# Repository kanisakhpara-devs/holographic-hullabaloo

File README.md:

# Holographic Hullabaloo
A spinning LED (Persistence of Vision) desk assistant which creates a "holographic" sarcastic 3D desk buddy.

### what is he talking about?

I understand your possibly dire confusion, so I'll try my best to explain it in the simplest way possible. Have you ever seen those LED fans which are all over Insta? They spin, to create an image.

The problem, however with those, is that they can only be viewed from one side, and properly from only one angle. Instead of engineering the solution, they are simply stuck on your wall, so it is only possible to view it from that exact point. Sometimes the best solutions are the most simple ones. Not in this case.

From this failure of a potential innovation sprouted a not very original, but a not-widely-done idea of an LED fan, but 3D, with AI integration, and sarcasm.

One may ask, why on earth would he do such a thing which would force him to spend hours upon hours coding and tuning the expression sequence loop? The short answer is, I'm speedrunning carpal tunnel. The long answer is that it would usually annoy me when those viral fans would call themselves high-tech, and 3d image viewer, and stuff like that, and nearly everyone who would buy them would end up disappointed. Or with their hand chopped off. But I built this mostly because it would look cool on my desk. (i hope u know im kidding)

$\color{orange}{\textsf{3D image + offline AI + Sass = Holographic Hullabaloo}}$
### how does it work?
2 blades with each a singular column of 72 LEDs, directly opposite each other, spin around a pivot at 1500 RPM, driven by a 775 motor, and rapidly flash in a coded sequence to create an image of a floating 3D face, which expresses and talks to you by recording your voice through the mic in the base, sending the audio through a USB cable to the laptop, where it gets transcribed and answered by a local Ollama-routed Gemma 3:4b, and then sending the answer back so the device speaks to you. Each response comes with an emotion tag, which tells the onboard ESP which expression to change to.

### how do I use it?
1. Plug in the 12V adapter to a wallsocket.
2. Connect the USB-C to the laptop. It should be recognized as a sound card.
3. Start the desktop app (Windows only, yet to be built)
4. Walk up to it and use the push-to-talk button (Wakeword will be toggleable)
5. When it senses that no one is around, it will stop spinning on its own in 10 minutes.

<details>
<summary>specs table</summary>

| Spec | Value |
| --- | --- |
| Display | Cylindrical POV, 100 mm across, 180 mm tall |
| Blades | 2, opposite each other at 50 mm radius |
| LEDs | 72 x APA102-2020 per blade (144 total), 2.5 mm pitch |
| Resolution | 72 rows x 200 columns per spin |
| Pixel size | 2.5 mm tall x 1.57 mm wide |
| Speed | 25 rev/s (1500 RPM) |
| Refresh | 50 Hz (2 blades) |
| Column time | 200 us |
| LED data | 4 parallel chains of 36, ESP32-S3 LCD peripheral, 12 MHz clock |
| Frame size | 43 KB (72 x 200 x 3 bytes), double buffered |
| Angle sensing | DRV5023 Hall sensor at 35 mm radius + 6 x 3 mm neodymium magnet, about 7.5 mm gap, about 19 mT at the sensor |
| Rotor MCU | ESP32-S3-WROOM-1-N8 (hub PCB) |
| Base MCU | ESP32-S3-WROOM-1-N8 (base PCB) |
| Rotor power | Wireless coil pair (12 V in, 5 V out, 43 mm coils, 3 mm gap) + 1S 1500 mAh LiPo backup |
| Rotor power chain | BQ24073 power-path charger (4.4 V out) -> TPS61088 boost (5.04 V) -> AMS1117 (3.3 V) |
| Rotor power draw | about 4 W typical, 5.2 W peak at 5 V (LED current capped at 0.8 A in firmware) |
| Base power | 12 V 3 A adapter -> MP1584 buck (5.0 V) through an SS34 diode, 470 uF bulk cap on 12 V for motor start |
| Motor | 12 V brushed 775, PI speed loop, hard cap about 28 rev/s |
| Audio | 40 mm 4 ohm 3 W speaker (MAX98357A, I2S) + INMP441 I2S mic |
| Laptop link | One USB-C cable: USB sound card + serial (native USB on the base ESP32-S3) |
| Base to rotor link | ESP-NOW, encrypted, MAC filtered, about 65 ms worst-case latency |
| AI | faster-whisper (speech to text), Gemma 3 4B via Ollama, Piper (text to speech), all local |
| Rotor frame | 2 x 104 x 30 x 3 mm aluminium bars, 2 x 10 x 10 x 1 mm angle posts, 4 L brackets |
| Cover | Rolled 1 mm polycarbonate, 125 mm across, 252 mm tall |
| Rotor mass | about 123 g |
| Blade force at speed | about 126 g, about 18 N per blade |
| Tip speed | about 7.9 m/s |
| Base | PETG, 140 mm across, 90 mm tall, removable floor |

</details>

<details>
<summary>CAD</summary>

Onshape (public): https://cad.onshape.com/documents/4085c279545975c6c33be840/w/43f94851c94c60cadccb3d5d/e/8ae002254131cced06da6b73

STEP files: [`cad/step/`](cad/step/)

| Module | What it is | STEP |
| --- | --- | --- |
| A | Rotor frame: 2 aluminium bars (104 x 30 x 3 mm), 2 angle posts, 4 L brackets | `A_frame_assembly_v3.step`, `A1_bottom_bar.step`, `A2_top_bar.step`, `A3_post.step`, `A4_bracket.step` |
| B | Blade PCB (190 mm, 72 LEDs) | `B1_Blade_v3_onshape.step` |
| C | Hub PCB placeholder (ESP32, coil, Hall, headers, USB-C on the flat edge) | `C_hub_placeholder.step` |
| D | Drive stack: 775 motor, flange coupling, coil pair, standoffs | `D_drive_stack.step` |
| E | Base v3: shell, removable floor, base PCB, speaker, mic | `E_base_v3_assembly.step`, `E1_base_shell_v3.step`, `E2_floor_plate.step`, `E3_base_pcb.step`, `E4_speaker_40mm.step`, `E5_INMP441_mic.step` |
| F | LiPo + polycarbonate cover + cap | `F_battery_cover.step` |
| All | Full assembly (34 parts) | `Fallen_full_assembly.step` |

| Fastener | Where |
| --- | --- |
| M2 x 6 | Blade PCB to angle post |
| M3 x 6 | L bracket to post |
| M3 x 8 | L bracket to bar, floor plate to base |
| M3 x 10 | Flange coupling to bottom bar |

| Integration check | Result |
| --- | --- |
| Interference check | 0 clashes across all 34 parts |
| Rotor centre of mass | 0.53 mm off axis, trimmed with about 2 g at r 35 mm |
| Cover clearance | 8.6 mm radial, 6.8 mm to the cap |
| Hall sensor vs magnet | r 34.5 mm vs r 35 mm |
| Coil gap | 3 mm |
| Motor shaft in coupling | 6.3 mm (13.5 mm standoffs) |
| Base board to motor | 13 mm clear |
| 470 uF cap to motor | 2.5 mm clear |
| DC jack to speaker connector | 9 mm clear |

</details>

<details>
<summary>cool blender renders</summary>

</details>

<details>
<summary>PCBs</summary>

| Board | Layers | Size | What's on it | Files |
| --- | --- | --- | --- | --- |
| Hub (rotor) | 2 | 80 mm disc with a flat edge for the USB-C, 12 mm centre hole | ESP32-S3, BQ24073 charger, TPS61088 boost, AMS1117, AO3401A switches, 74AHCT245 LED buffer, DRV5023 Hall, USB-C, RX coil header, LiPo JST | [`pcb/hub`](pcb/hub) |
| Blade (x2) | 4 (inner GND + 5V planes) | 190 mm long, wire tab at the bottom | 72 x APA102-2020 in 2 chains of 36, 100 nF per LED | [`pcb/blade`](pcb/blade) |
| Base | 2 | 96 x 99.5 mm | ESP32-S3 (native USB), MAX98357A amp, AO4406A motor driver, USB-C, AMS1117, SS34 buck diode, 470 uF 12 V bulk cap, headers for mic, ToF sensors, buck, button | [`pcb/base`](pcb/base) |

All three: KiCad 10, ERC 0 errors, DRC 0 errors / 0 unconnected, `gerbers.zip` in each folder. JLCPCB standard specs (HASL, 0.15 mm clearance). Hub and base use 0.3 mm min drill; the 4-layer blade uses 0.45 / 0.2 mm vias. JLC assembly files (BOM + pick and place) for the hub and base are in their folders as `*_bom_jlc.csv` and `*_cpl_jlc.csv`.

**$\color{violet}{\textsf{hub}}$**

**$\color{violet}{\textsf{blade}}$**

**$\color{violet}{\textsf{base}}$**

</details>

<details>
<summary>firmware</summary>

PlatformIO + Arduino, untested on hardware. Both projects compile.

| Folder | Runs on | Job |
| --- | --- | --- |
| `firmware/rotor` | Hub ESP32-S3 | Hall timing, column timer, LED DMA output, frame buffers, face layers, ESP-NOW receive, battery/power |
| `firmware/base` | Base ESP32-S3 | Motor soft start + PI speed loop, ToF sensors, talk button, USB serial link, ESP-NOW send |
| `firmware/shared` | Both | `packet.h`: state + status packets, magic/version/type/sequence header, CRC-8 |

Build: `cd firmware/base && pio run` (same for `firmware/rotor`).

Known gaps: the USB sound card on the base needs ESP-IDF / TinyUSB UAC (the Arduino core doesn't include USB audio), and the rotor needs a half-column timing offset where the LED chains meet at mid-blade.

**Base pin map (ESP32-S3)**

| GPIO | Function |
| --- | --- |
| IO4 | Motor PWM (AO4406A gate) |
| IO5 | Talk button |
| IO6 / IO7 | ToF front / back XSHUT |
| IO8 / IO9 | I2C SDA / SCL |
| IO12 / IO13 / IO14 | Amp BCLK / LRC / DIN |
| IO15 | Amp enable |
| IO16 / IO17 / IO18 | Mic SCK / WS / SD |
| IO21 | Status LED |
| IO19 / IO20 | USB D- / D+ |

**Rotor pin map (ESP32-S3)**

| GPIO | Function |
| --- | --- |
| IO1 | Battery voltage (ADC, 100k/100k divider) |
| IO4 | Hall sensor (falling edge capture) |
| IO5 / IO6 | Charger PGOOD / CHG |
| IO7 | LED power enable |
| IO8 | Status LED |
| IO9 | LED clock |
| IO10 to IO13 | LED data, 4 chains |
| IO19 / IO20 | USB D- / D+ |

</details>

<details>
<summary>bill of materials (BOM)</summary>

Full list with a link for every part: [`bom.csv`](bom.csv)

**Total: about $492.43 (Rs 46,292)** at Rs 94 = $1. JLC fab, assembly and shipping lines are estimates until the real quote. Aluminium bar and angle are bought locally in Mumbai; their links are price references.

| Group | Main parts |
| --- | --- |
| LEDs | 160 x APA102-2020 (Adafruit 3341, DigiKey India), 144 used + 16 spares |
| PCBs | Hub + base (JLC PCBA), 5 x 4-layer blades, stencil |
| Rotor electronics | ESP32-S3-WROOM-1-N8, BQ24073, TPS61088, AMS1117, 74AHCT245, DRV5023, passives |
| Base electronics | ESP32-S3-WROOM-1-N8, MAX98357A, AO4406A, INMP441, 40 mm speaker, 2 x VL53L0X, MP1584 buck, 470 uF cap |
| Power | Wireless coil pair, 2 ferrite sheets, 1S 1500 mAh LiPo, 12 V 3 A adapter |
| Mechanical | 775 motor, 5 mm flange coupling, 30 x 3 mm aluminium flat bar + 10 x 10 mm angle, 6 x 3 mm magnet, nylon standoffs, M2/M3 hardware, heat-set inserts |
| Enclosure | PETG, 1 mm polycarbonate sheet, primer + matte black paint |
| Tools | Hot air station (858D), solder paste (Sn42/Bi58), solder wire, hacksaw, file, pin vise drill, Allen keys, IPA, fume extractor |

</details>

<details>
<summary>how it evolved (non-darwinian)</summary>

```diff
@@ v0.1 . Nov 8 @@
- self-balancing jumping cube
+ spinning POV hologram
  because: i dont like physics

@@ v0.2 . Nov 8 @@
- flat LED fan, only readable from the front
+ cylinder you can walk around

@@ v0.3 . Nov 8 @@
- 48 rows of LEDs
+ 72 rows
  because: 48 pixels tall can't do facial expressions

@@ v0.4 . Nov 9 @@
- 1 blade + the battery as a counterweight
+ 2 blades
  because: 25 Hz flickers, and the battery was 2 to 3x too heavy to balance it

@@ v0.5 . Nov 9 @@
- battery only
+ wireless power coil, battery as backup
  because: no cable survives 1500 RPM

@@ v0.6 . Nov 9 @@
- 1 LED chain
+ 4 parallel chains
  because: one chain took the whole column time and vertical lines came out slanted

@@ v0.7 . Nov 9 @@
- Hall sensor at 15 mm, then 30 mm
+ Hall sensor at 35 mm
  because: it was sitting on top of the coil. twice

@@ v0.8 . Nov 10 @@
- JLC LEDs at 2.0 / 2.2 mm pitch
+ 160 Adafruit LEDs at 2.5 mm pitch, hand soldered
  because: every single listing had 0 stock, and the datasheet pads were too wide anyway

@@ v0.9 . Nov 11 @@
- BQ24072 charger
+ BQ24073 charger
  because: the 24072 output follows the battery, the 24073 holds a steady 4.4 V
+ first time ever opening KiCad

@@ v0.10 . Nov 17 @@
- 125 mm bars
+ 104 mm bars
  because: they would have hit the cover

@@ v0.11 . Nov 18 @@
- 2 layer blade PCB
+ 4 layer blade PCB
  because: 72 LEDs need solid power planes

@@ v0.12 . Nov 18 @@
- 240 mm cover, 15 mm standoffs
+ 252 mm cover, 13.5 mm standoffs
  because: the LiPo moved on top of the top bar, and the motor shaft barely reached the coupling

@@ v0.13 . Nov 19 @@
- the laptop's mic and speakers
+ speaker + mic in the base

@@ v0.14 . Nov 19 @@
- a dev board I already owned
+ a custom base PCB
  because: Fallen won't fund dev boards, and the BOM somehow had no base microcontroller or motor driver at all

@@ v0.15 . Nov 19 @@
- one-piece base
+ base with a removable floor
  because: the only way inside the old one was a 44 mm hole

@@ v1.0 . Nov 20 (submission day) @@
- 25 mm bars, M2 x 8 bolts
+ 30 mm bars, M2 x 6 bolts
  because: the bolts were trying to occupy the same space. physics said no
- hub USB-C on the round edge
+ hub USB-C on a new flat edge
  because: no plug could reach it
- buck straight onto the 5 V rail
+ diode on the buck + a 470 uF cap on 12 V
  because: USB and the buck could fight each other, and motor start dips the 12 V rail
- DC jack in the base wall
+ DC jack moved lower
  because: it was sitting on top of the speaker connector
```

</details>

<details>
<summary>ai usage</summary>

| Area | What I did | What AI (Claude) did |
| --- | --- | --- |
| Design decisions | Made every decision | Did calculations and scraped datasheets |
| Hub schematic | Drew all 3 sheets in KiCad | Gave a guide |
| Blade schematic | Drew it, made the LED symbol + footprint | Gave a guide|
| Hub layout | Placement, boost SW node / BOOT / VIN routing, GND pours, antenna keepout | Part of the placement, rest of the boost loop.|
| Blade layout | Picked the options (4-layer, wire tab, chain direction) | Built and routed the whole board by script (72 LEDs in a row) |
| Base PCB | Picked out solutions and proposed ideas and concepts| Made the layout and routing by script |
| CAD | All part studios and appearances | Made dimensioned sketches and carried out interference checks |
| Design review | Decided every fix (bar width, buck diode, 470 uF placement) | Cross-checked CAD, PCBs and BOM against each other. |
| Firmware | Reviewed it | Wrote the skeleton |
| Renders | Artistic direction | Blender scene and render scripts |
| BOM | Built the sheet, sourcing calls | Looked up parts and stock, filled rows |
| Journals | All of it | Nothing |
| This README | Wrote it | Section outline and number tables |

</details>

<details>
<summary>status and what's next?</summary>

| Part | Status |
| --- | --- |
| Calculations | Done ([`docs/calculations.md`](docs/calculations.md)) |
| Hub PCB | Designed, ERC/DRC clean, gerbers ready |
| Blade PCB | Designed, DRC clean, gerbers ready |
| Base PCB | Designed, ERC/DRC clean, gerbers ready |
| CAD | Done, 0 interferences, public on Onshape |
| Firmware | Skeleton, compiles, untested |
| Laptop app (STT, LLM, TTS) | Not started |
| Build | Waiting for design approval and parts |

Next: order PCBs and parts, build the base and spin a dummy rotor, bench-test the wireless coil, solder the blades, bring up the hub, get a static image stable, then the face, then the AI loop. Target: working and filmed by Dec 4.

</details>

<details>
<summary>LICENCE</summary>

MIT, see [LICENCE](LICENCE).

</details>

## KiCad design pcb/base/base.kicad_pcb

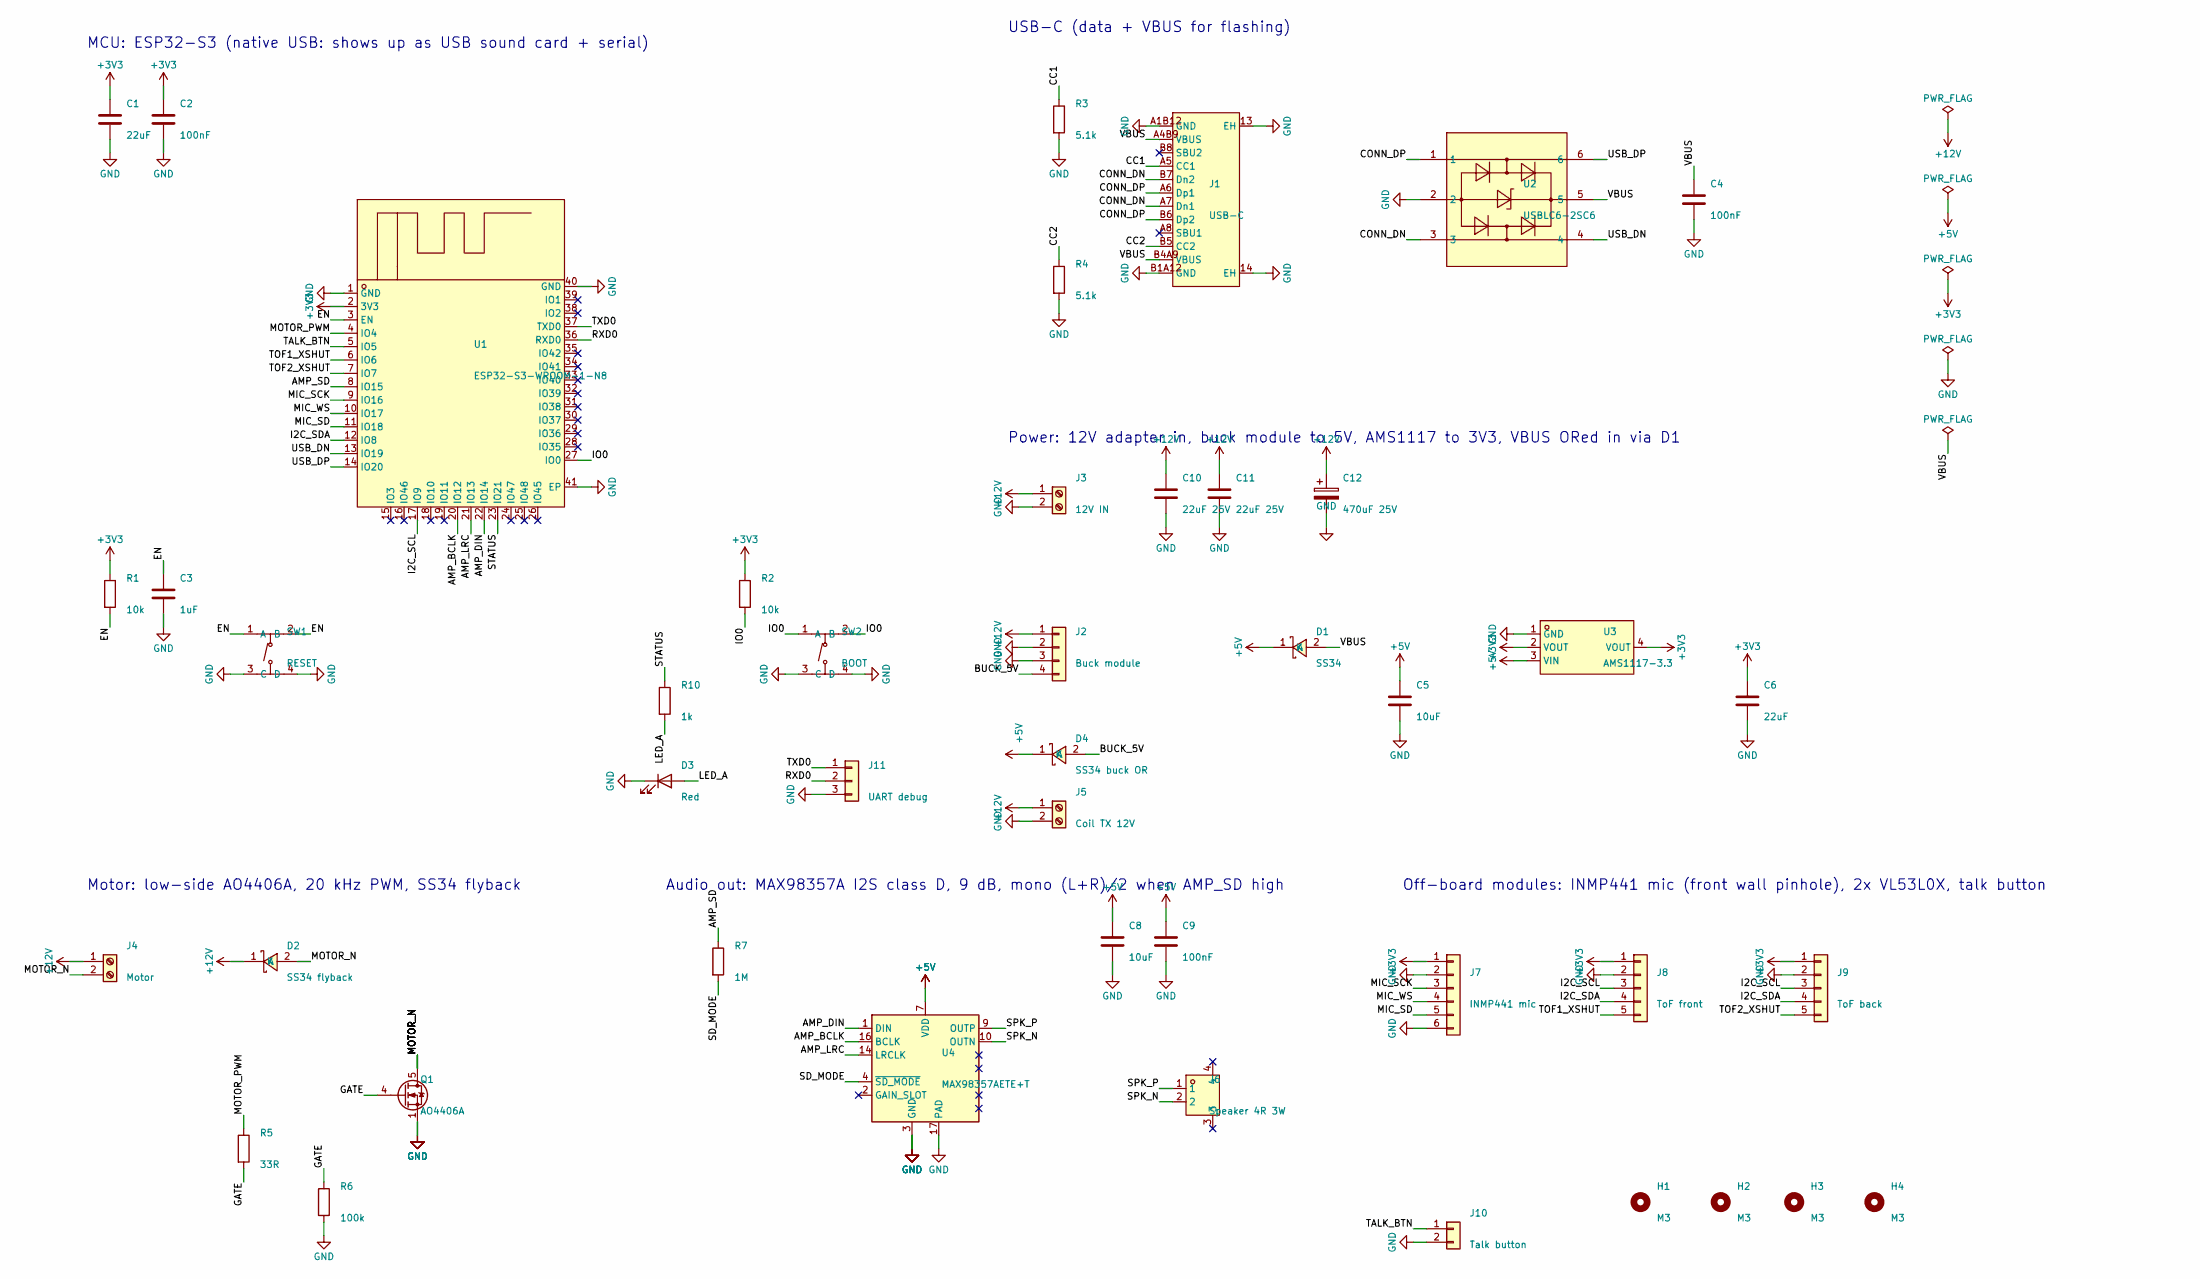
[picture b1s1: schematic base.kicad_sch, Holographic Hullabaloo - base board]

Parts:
C1, C6: 22uF; C_0805_2012Metric; LCSC Part C45783
C2, C4, C9: 100nF; C_0402_1005Metric; LCSC Part C1525
C3: 1uF; C_0402_1005Metric; LCSC Part C52923
C5, C8: 10uF; C_0603_1608Metric; LCSC Part C19702
C10, C11: 22uF 25V; C_0805_2012Metric; LCSC Part C45783
C12: 470uF 25V; CP_Elec_8x10.5; LCSC Part C1984855
D1: SS34; SMA_L4.3-W2.6-LS5.2-RD; LCSC Part C8678
D2: SS34 flyback; SMA_L4.3-W2.6-LS5.2-RD; LCSC Part C8678
D3: Red; LED_0603_1608Metric; LCSC Part C2286
D4: SS34 buck OR; SMA_L4.3-W2.6-LS5.2-RD; LCSC Part C8678
H1, H2, H3, H4: M3; MountingHole_3.2mm_M3
J1: USB-C; USB-C-SMD_TYPE-C-16PIN-2MD-073; LCSC Part C2765186
J2: Buck module; PinHeader_1x04_P2.54mm_Vertical
J3: 12V IN; TerminalBlock_Phoenix_MKDS-1,5-2-5.08_1x02_P5.08mm_Horizont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
J4: Motor; TerminalBlock_Phoenix_MKDS-1,5-2-5.08_1x02_P5.08mm_Horizont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
J5: Coil TX 12V; TerminalBlock_Phoenix_MKDS-1,5-2-5.08_1x02_P5.08mm_Horizont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
J6: Speaker 4R 3W; CONN-SMD_P2.00_S2B-PH-SM4-TB-LF-SN; LCSC Part C295747
J7: INMP441 mic; PinHeader_1x06_P2.54mm_Vertical
J8: ToF front; PinHeader_1x05_P2.54mm_Vertical
J9: ToF back; PinHeader_1x05_P2.54mm_Vertical
J10: Talk button; PinHeader_1x02_P2.54mm_Vertical
J11: UART debug; PinHeader_1x03_P2.54mm_Vertical
Q1: AO4406A; SOIC-8_3.9x4.9mm_P1.27mm; LCSC Part C2944312
R1, R2: 10k; R_0402_1005Metric; LCSC Part C25744
R3, R4: 5.1k; R_0402_1005Metric; LCSC Part C25905
R5: 33R; R_0402_1005Metric; LCSC Part C25105
R6: 100k; R_0402_1005Metric; LCSC Part C25741
R7: 1M; R_0402_1005Metric; LCSC Part C26083
R10: 1k; R_0402_1005Metric; LCSC Part C11702
SW1: RESET; SW-SMD_4P-L5.1-W5.1-P3.70-LS6.5-TL_H1.5; LCSC Part C318884
SW2: BOOT; SW-SMD_4P-L5.1-W5.1-P3.70-LS6.5-TL_H1.5; LCSC Part C318884
U1: ESP32-S3-WROOM-1-N8; WIFIM-SMD_ESP32-S3-WROOM-1-N8; LCSC Part C2913198
U2: USBLC6-2SC6; SOT-23-6_L2.9-W1.6-P0.95-LS2.8-BL; LCSC Part C7519
U3: AMS1117-3.3; SOT-223-3_L6.5-W3.4-P2.30-LS7.0-BR; LCSC Part C6186
U4: MAX98357AETE+T; TQFN-16-1EP_3x3mm_P0.5mm_EP1.23x1.23mm; LCSC Part C910544

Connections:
+3V3: C1.1, C2.1, C6.1, J7.1, J8.1, J9.1, R1.1, R2.1, U1.2 (3V3), U3.2 (VOUT), U3.4 (VOUT)
+5V: C5.1, C8.1, C9.1, D1.1 (K), D4.1 (K), U3.3 (VIN), U4.7 (VDD), U4.8 (VDD)
+12V: C10.1, C11.1, C12.1, D2.1 (K), J2.1, J3.1, J4.1, J5.1
/AMP_BCLK: U1.20 (IO12), U4.16 (BCLK)
/AMP_DIN: U1.22 (IO14), U4.1 (DIN)
/AMP_LRC: U1.21 (IO13), U4.14 (LRCLK)
/AMP_SD: R7.1, U1.8 (IO15)
/BUCK_5V: D4.2 (A), J2.4
/CC1: J1.A5 (CC1), R3.1
/CC2: J1.B5 (CC2), R4.1
/CONN_DN: J1.A7 (Dn1), J1.B7 (Dn2), U2.3
/CONN_DP: J1.A6 (Dp1), J1.B6 (Dp2), U2.1
/EN: C3.1, R1.2, SW1.1 (A), SW1.2 (B), U1.3 (EN)
/GATE: Q1.4 (G), R5.2, R6.1
/I2C_SCL: J8.3, J9.3, U1.17 (IO9)
/I2C_SDA: J8.4, J9.4, U1.12 (IO8)
/IO0: R2.2, SW2.1 (A), SW2.2 (B), U1.27 (IO0)
/LED_A: D3.2 (A), R10.2
/MIC_SCK: J7.3, U1.9 (IO16)
/MIC_SD: J7.5, U1.11 (IO18)
/MIC_WS: J7.4, U1.10 (IO17)
/MOTOR_N: D2.2 (A), J4.2, Q1.5 (D), Q1.6 (D), Q1.7 (D), Q1.8 (D)
/MOTOR_PWM: R5.1, U1.4 (IO4)
/RXD0: J11.2, U1.36 (RXD0)
/SD_MODE: R7.2, U4.4 (~SD_MODE)
/SPK_N: J6.2, U4.10 (OUTN)
/SPK_P: J6.1, U4.9 (OUTP)
/STATUS: R10.1, U1.23 (IO21)
/TALK_BTN: J10.1, U1.5 (IO5)
/TOF1_XSHUT: J8.5, U1.6 (IO6)
/TOF2_XSHUT: J9.5, U1.7 (IO7)
/TXD0: J11.1, U1.37 (TXD0)
/USB_DN: U1.13 (IO19), U2.4
/USB_DP: U1.14 (IO20), U2.6
/VBUS: C4.1, D1.2 (A), J1.A4B9 (VBUS), J1.B4A9 (VBUS), U2.5
GND: C1.2, C2.2, C3.2, C4.2, C5.2, C6.2, C8.2, C9.2, C10.2, C11.2, C12.2, D3.1 (K), J1.13 (EH), J1.14 (EH), J1.A1B12 (GND), J1.B1A12 (GND), J2.2, J2.3, J3.2, J5.2, J7.2, J7.6, J8.2, J9.2, J10.2, J11.3, Q1.1 (S), Q1.2 (S), Q1.3 (S), R3.2, R4.2, R6.2, SW1.3 (C), SW1.4 (D), SW2.3 (C), SW2.4 (D), U1.1 (GND), U1.40 (GND), U1.41 (EP), U2.2, U3.1 (GND), U4.3 (GND), U4.11 (GND), U4.15 (GND), U4.17 (PAD)

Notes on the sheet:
MCU: ESP32-S3 (native USB: shows up as USB sound card + serial)
USB-C (data + VBUS for flashing)
Power: 12V adapter in, buck module to 5V, AMS1117 to 3V3, VBUS ORed in via D1
Motor: low-side AO4406A, 20 kHz PWM, SS34 flyback
Audio out: MAX98357A I2S class D, 9 dB, mono (L+R)/2 when AMP_SD high
Off-board modules: INMP441 mic (front wall pinhole), 2x VL53L0X, talk button

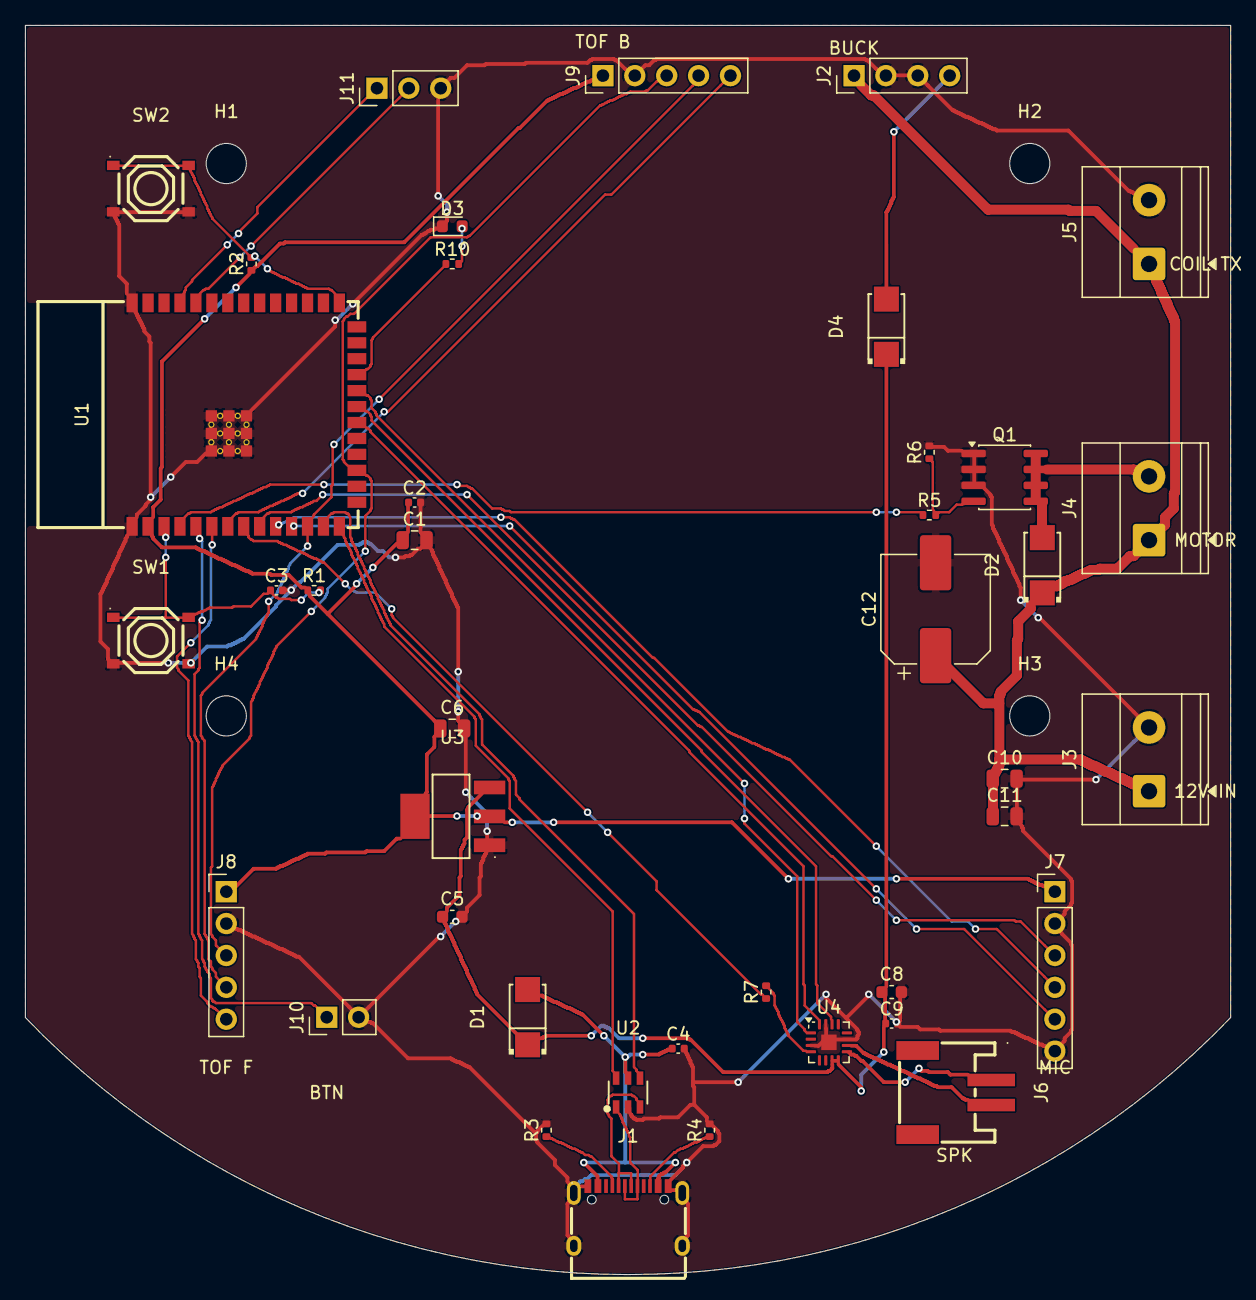
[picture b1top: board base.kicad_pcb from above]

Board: 2 copper layers, 96.0 x 99.5 mm, 45 parts (0 on the bottom side), 36 nets.

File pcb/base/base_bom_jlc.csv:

"Comment","Designator","Footprint","LCSC Part #"
"22uF","C1,C6","Capacitor_SMD:C_0805_2012Metric","C45783"
"100nF","C2,C4,C9","Capacitor_SMD:C_0402_1005Metric","C1525"
"1uF","C3","Capacitor_SMD:C_0402_1005Metric","C52923"
"10uF","C5,C8","Capacitor_SMD:C_0603_1608Metric","C19702"
"22uF 25V","C10,C11","Capacitor_SMD:C_0805_2012Metric","C45783"
"470uF 25V","C12","Capacitor_SMD:CP_Elec_8x10.5","C1984855"
"SS34","D1","fallen:SMA_L4.3-W2.6-LS5.2-RD","C8678"
"SS34 flyback","D2","fallen:SMA_L4.3-W2.6-LS5.2-RD","C8678"
"Red","D3","LED_SMD:LED_0603_1608Metric","C2286"
"SS34 buck OR","D4","fallen:SMA_L4.3-W2.6-LS5.2-RD","C8678"
"USB-C","J1","fallen:USB-C-SMD_TYPE-C-16PIN-2MD-073","C2765186"
"Buck module","J2","Connector_PinHeader_2.54mm:PinHeader_1x04_P2.54mm_Vertical",""
"12V IN","J3","TerminalBlock_Phoenix:TerminalBlock_Phoenix_MKDS-1,5-2-5.08_1x02_P5.08mm_Horizontal",""
"Motor","J4","TerminalBlock_Phoenix:TerminalBlock_Phoenix_MKDS-1,5-2-5.08_1x02_P5.08mm_Horizontal",""
"Coil TX 12V","J5","TerminalBlock_Phoenix:TerminalBlock_Phoenix_MKDS-1,5-2-5.08_1x02_P5.08mm_Horizontal",""
"Speaker 4R 3W","J6","fallen:CONN-SMD_P2.00_S2B-PH-SM4-TB-LF-SN","C295747"
"INMP441 mic","J7","Connector_PinHeader_2.54mm:PinHeader_1x06_P2.54mm_Vertical",""
"ToF front","J8","Connector_PinHeader_2.54mm:PinHeader_1x05_P2.54mm_Vertical",""
"ToF back","J9","Connector_PinHeader_2.54mm:PinHeader_1x05_P2.54mm_Vertical",""
"Talk button","J10","Connector_PinHeader_2.54mm:PinHeader_1x02_P2.54mm_Vertical",""
"UART debug","J11","Connector_PinHeader_2.54mm:PinHeader_1x03_P2.54mm_Vertical",""
"AO4406A","Q1","Package_SO:SOIC-8_3.9x4.9mm_P1.27mm","C2944312"
"10k","R1,R2","Resistor_SMD:R_0402_1005Metric","C25744"
"5.1k","R3,R4","Resistor_SMD:R_0402_1005Metric","C25905"
"33R","R5","Resistor_SMD:R_0402_1005Metric","C25105"
"100k","R6","Resistor_SMD:R_0402_1005Metric","C25741"
"1M","R7","Resistor_SMD:R_0402_1005Metric","C26083"
"1k","R10","Resistor_SMD:R_0402_1005Metric","C11702"
"RESET","SW1","fallen:SW-SMD_4P-L5.1-W5.1-P3.70-LS6.5-TL_H1.5","C318884"
"BOOT","SW2","fallen:SW-SMD_4P-L5.1-W5.1-P3.70-LS6.5-TL_H1.5","C318884"
"ESP32-S3-WROOM-1-N8","U1","fallen:WIFIM-SMD_ESP32-S3-WROOM-1-N8","C2913198"
"USBLC6-2SC6","U2","fallen:SOT-23-6_L2.9-W1.6-P0.95-LS2.8-BL","C7519"
"AMS1117-3.3","U3","fallen:SOT-223-3_L6.5-W3.4-P2.30-LS7.0-BR","C6186"
"MAX98357AETE+T","U4","Package_DFN_QFN:TQFN-16-1EP_3x3mm_P0.5mm_EP1.23x1.23mm","C910544"

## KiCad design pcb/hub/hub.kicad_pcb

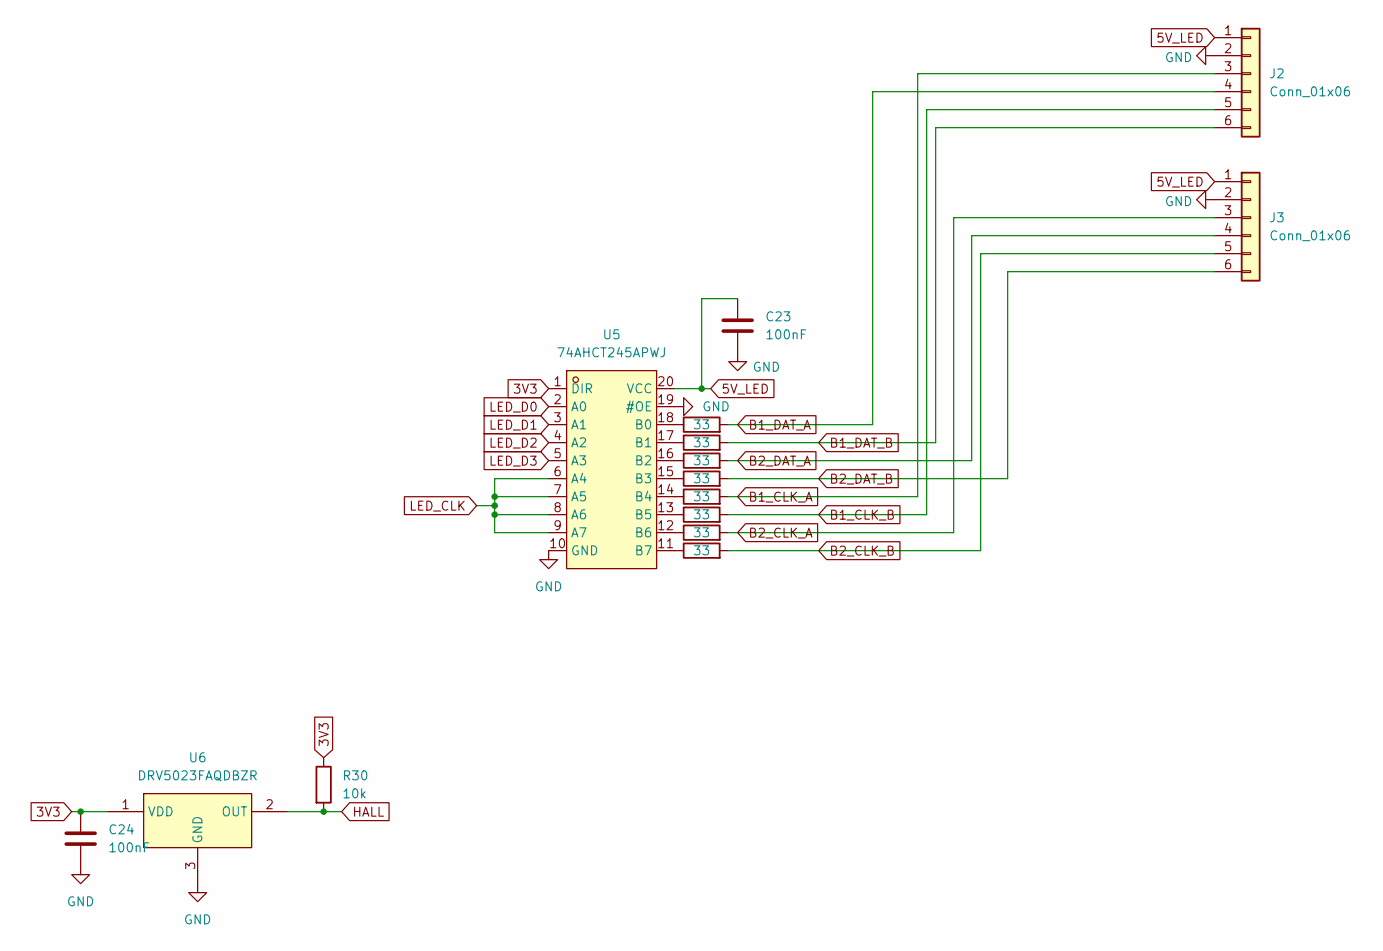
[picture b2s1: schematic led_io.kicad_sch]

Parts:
C23, C24: 100nF; C_0402_1005Metric; LCSC Part C1525
J2, J3: Conn_01x06; PinHeader_1x06_P2.54mm_Vertical
R22, R23, R24, R25, R26, R27, R28, R29: 33; R_0402_1005Metric; LCSC Part C25105
R30: 10k; R_0402_1005Metric; LCSC Part C25744
U5: 74AHCT245APWJ; TSSOP-20_L6.5-W4.4-P0.65-LS6.4-BL; MPN 74AHCT245APWJ; LCSC Part C554610
U6: DRV5023FAQDBZR; SOT-23-3_L2.9-W1.6-P1.90-LS2.8-BR; MPN DRV5023FAQDBZR; LCSC Part C114983

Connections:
3V3: C24.1, R30.1, U5.1 (DIR), U6.1 (VDD); also elsewhere on the board
5V_LED: C23.1, J2.1, J3.1, U5.20 (VCC); also elsewhere on the board
B1_CLK_A: J2.3, R26.2
B1_CLK_B: J2.5, R27.2
B1_DAT_A: J2.4, R22.2
B1_DAT_B: J2.6, R23.2
B2_CLK_A: J3.3, R28.2
B2_CLK_B: J3.5, R29.2
B2_DAT_A: J3.4, R24.2
B2_DAT_B: J3.6, R25.2
GND: C23.2, C24.2, J2.2, J3.2, U5.10 (GND), U5.19 (#OE), U6.3 (GND); also elsewhere on the board
HALL: R30.2, U6.2 (OUT); also elsewhere on the board
LED_CLK: U5.6 (A4), U5.7 (A5), U5.8 (A6), U5.9 (A7); also elsewhere on the board
LED_D0: U5.2 (A0); also elsewhere on the board
LED_D1: U5.3 (A1); also elsewhere on the board
LED_D2: U5.4 (A2); also elsewhere on the board
LED_D3: U5.5 (A3); also elsewhere on the board
unnamed: R22.1, U5.18 (B0)
unnamed: R23.1, U5.17 (B1)
unnamed: R24.1, U5.16 (B2)
unnamed: R25.1, U5.15 (B3)
unnamed: R26.1, U5.14 (B4)
unnamed: R27.1, U5.13 (B5)
unnamed: R28.1, U5.12 (B6)
unnamed: R29.1, U5.11 (B7)

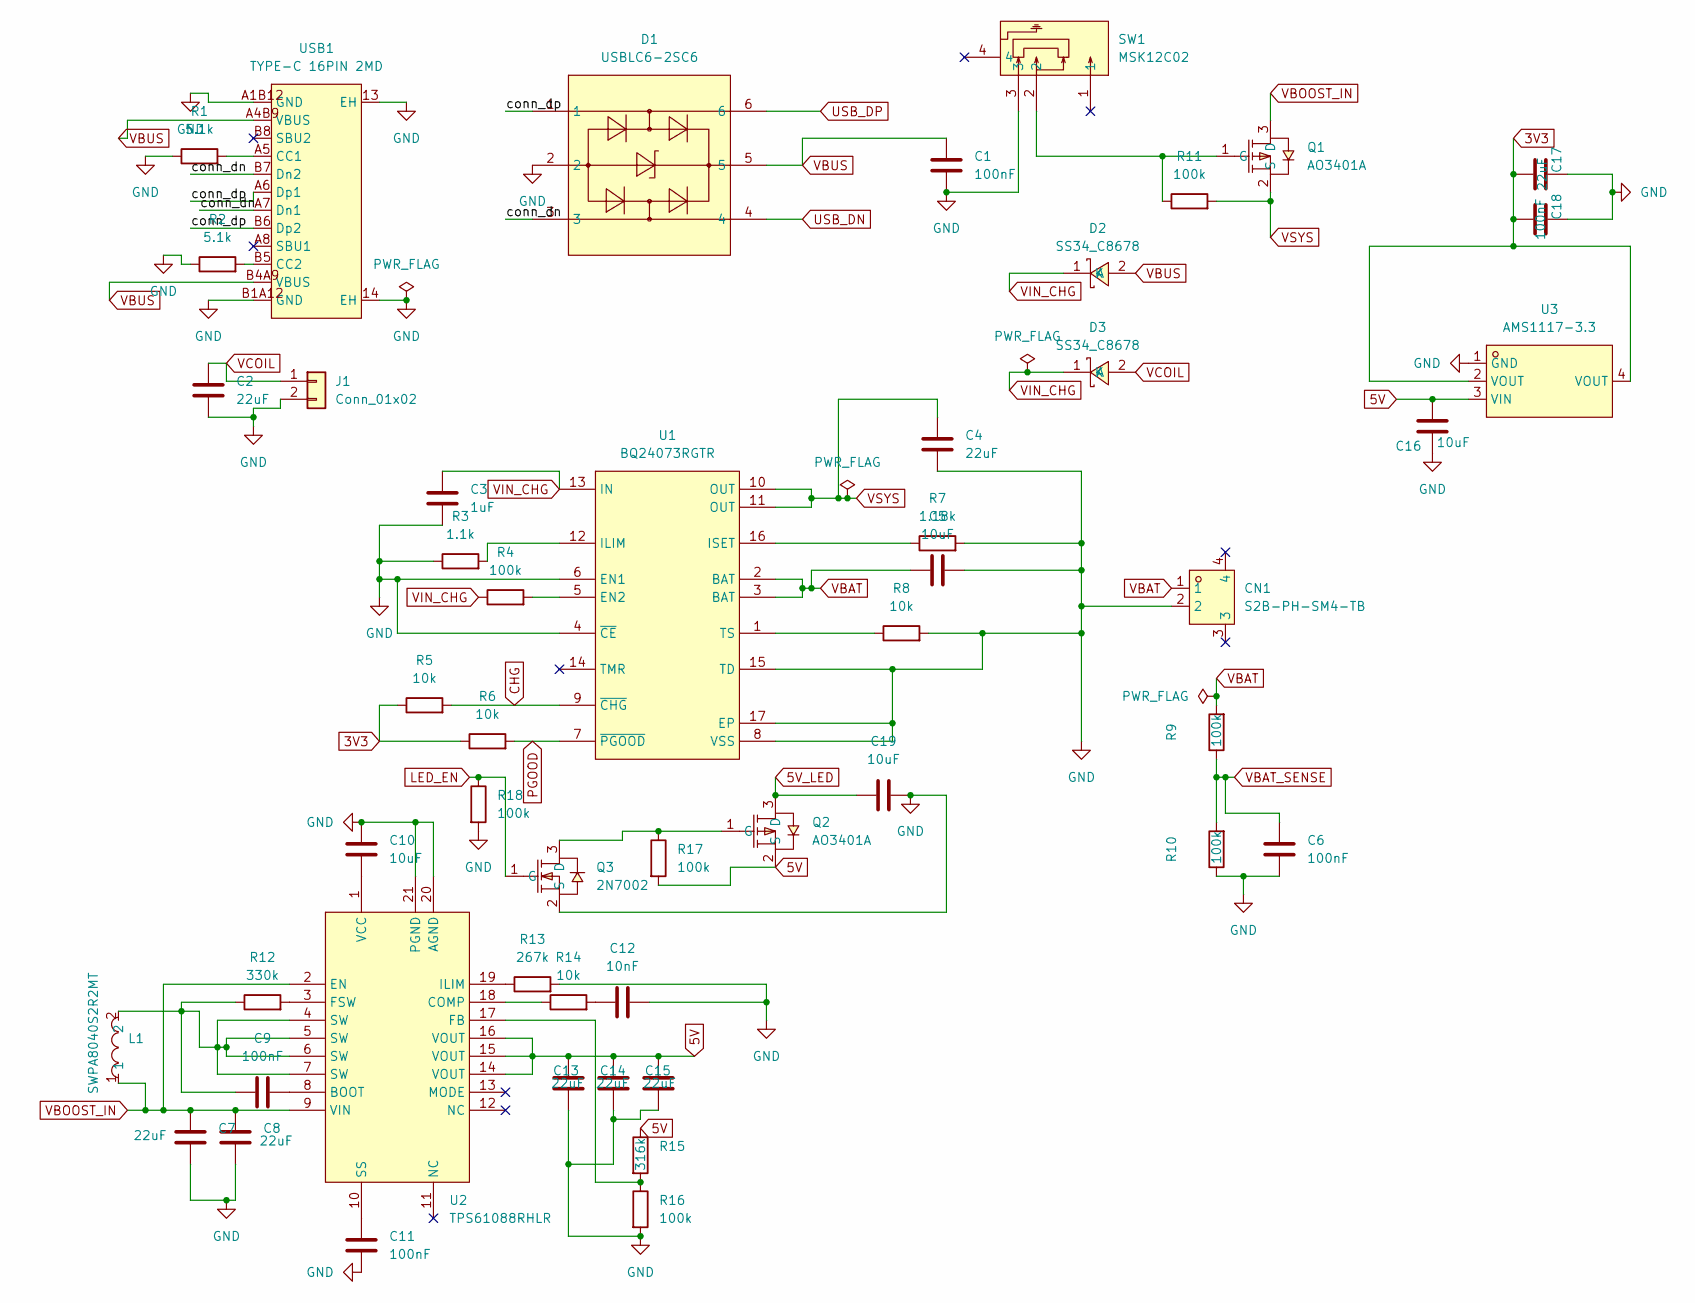
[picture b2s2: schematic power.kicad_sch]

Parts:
C1, C6, C9, C11, C18: 100nF; C_0402_1005Metric; LCSC Part C1525
C2, C4, C7, C8, C13, C14, C15, C17: 22uF; C_0805_2012Metric; LCSC Part C45783
C3: 1uF; C_0402_1005Metric; LCSC Part C52923
C5, C10, C16, C19: 10uF; C_0603_1608Metric; LCSC Part C19702
C12: 10nF; C_0402_1005Metric; LCSC Part C15195
CN1: S2B-PH-SM4-TB; CONN-SMD_P2.00_S2B-PH-SM4-TB-LF-SN; MPN S2B-PH-SM4-TB(LF)(SN); LCSC Part C295747
D1: USBLC6-2SC6; SOT-23-6_L2.9-W1.6-P0.95-LS2.8-BL; MPN USBLC6-2SC6; LCSC Part C7519
D2, D3: SS34_C8678; SMA_L4.3-W2.6-LS5.2-RD; MPN SS34; LCSC Part C8678
J1: Conn_01x02; PinHeader_1x02_P2.54mm_Vertical
L1: SWPA8040S2R2MT; IND-SMD_L8.0-W8.0_SWPA8040S; MPN SWPA8040S2R2MT; LCSC Part C36415
Q1, Q2: AO3401A; SOT-23_L2.9-W1.3-P1.90-LS2.4-BR; MPN AO3401A; LCSC Part C15127
Q3: 2N7002; SOT-23-3_L2.9-W1.3-P1.90-LS2.4-BR; MPN 2N7002; LCSC Part C8545
R1, R2: 5.1k; R_0402_1005Metric; LCSC Part C25905
R3: 1.1k; R_0402_1005Metric; LCSC Part C482070
R4, R9, R10, R11, R16, R17, R18: 100k; R_0402_1005Metric; LCSC Part C25741
R5, R6, R8, R14: 10k; R_0402_1005Metric; LCSC Part C25744
R7: 1.18k; R_0402_1005Metric; LCSC Part C2092244
R12: 330k; R_0402_1005Metric; LCSC Part C102977
R13: 267k; R_0402_1005Metric; LCSC Part C2998050
R15: 316k; R_0402_1005Metric; LCSC Part C25777
SW1: MSK12C02; SW-TH_MSK12C02; MPN MSK12C02; LCSC Part C431540
U1: BQ24073RGTR; QFN-16_L3.0-W3.0-P0.50-TL-EP1.7; MPN BQ24073RGTR; LCSC Part C15220
U2: TPS61088RHLR; VQFN-20_L4.6-W3.6-P0.50-BL; MPN TPS61088RHLR; LCSC Part C87357
U3: AMS1117-3.3; SOT-223-3_L6.5-W3.4-P2.30-LS7.0-BR; MPN AMS1117-3.3; LCSC Part C6186
USB1: TYPE-C 16PIN 2MD; USB-C-SMD_TYPE-C-16PIN-2MD-073; MPN TYPE-C 16PIN 2MD(073); LCSC Part C2765186

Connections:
3V3: C17.1, C18.1, R5.1, R6.1, U3.2 (VOUT), U3.4 (VOUT); also elsewhere on the board
5V: C13.1, C14.1, C15.1, C16.1, Q2.2 (S), R15.1, R17.2, U2.14 (VOUT), U2.15 (VOUT), U2.16 (VOUT), U3.3 (VIN)
5V_LED: C19.1, Q2.3 (D); also elsewhere on the board
/power/conn_dn: D1.3, USB1.A7 (Dn1), USB1.B7 (Dn2)
/power/conn_dp: D1.1, USB1.A6 (Dp1), USB1.B6 (Dp2)
CHG: R5.2, U1.9 (~CHG); also elsewhere on the board
GND: C1.2, C2.2, C3.2, C4.2, C5.2, C6.2, C7.2, C8.2, C10.1, C11.2, C12.2, C13.2, C14.2, C15.2, C16.2, C17.2, C18.2, C19.2, CN1.2, D1.2, J1.2, Q3.2 (S), R1.1, R2.1, R3.1, R7.2, R8.2, R10.1, R13.2, R16.2, R18.2, SW1.3, U1.4 (~CE), U1.6 (EN1), U1.8 (VSS), U1.15 (TD), U1.17 (EP), U2.20 (AGND), U2.21 (PGND), U3.1 (GND), USB1.13 (EH), USB1.14 (EH), USB1.A1B12 (GND), USB1.B1A12 (GND); also elsewhere on the board
LED_EN: Q3.1 (G), R18.1; also elsewhere on the board
unnamed: C9.1, L1.2, R12.1, U2.4 (SW), U2.5 (SW), U2.6 (SW), U2.7 (SW)
unnamed: C12.1, R14.2
unnamed: Q1.1 (G), R11.1, SW1.2
unnamed: Q2.1 (G), Q3.3 (D), R17.1
unnamed: R4.2, U1.5 (EN2)
unnamed: R3.2, U1.12 (ILIM)
unnamed: R7.1, U1.16 (ISET)
unnamed: R8.1, U1.1 (TS)
unnamed: C9.2, U2.8 (BOOT)
unnamed: R14.1, U2.18 (COMP)
unnamed: R15.2, R16.1, U2.17 (FB)
unnamed: R12.2, U2.3 (FSW)
unnamed: R13.1, U2.19 (ILIM)
unnamed: C11.1, U2.10 (SS)
unnamed: C10.2, U2.1 (VCC)
unnamed: R1.2, USB1.A5 (CC1)
unnamed: R2.2, USB1.B5 (CC2)
PGOOD: R6.2, U1.7 (~PGOOD); also elsewhere on the board
USB_DN: D1.4; also elsewhere on the board
USB_DP: D1.6; also elsewhere on the board
VBAT: C5.1, CN1.1, R9.2, U1.2 (BAT), U1.3 (BAT)
VBAT_SENSE: C6.1, R9.1, R10.2; also elsewhere on the board
VBOOST_IN: C7.1, C8.1, L1.1, Q1.3 (D), U2.2 (EN), U2.9 (VIN)
VBUS: C1.1, D1.5, D2.2 (A), USB1.A4B9 (VBUS), USB1.B4A9 (VBUS)
VCOIL: C2.1, D3.2 (A), J1.1
VIN_CHG: C3.1, D2.1 (K), D3.1 (K), R4.1, U1.13 (IN)
VSYS: C4.1, Q1.2 (S), R11.2, U1.10 (OUT), U1.11 (OUT)

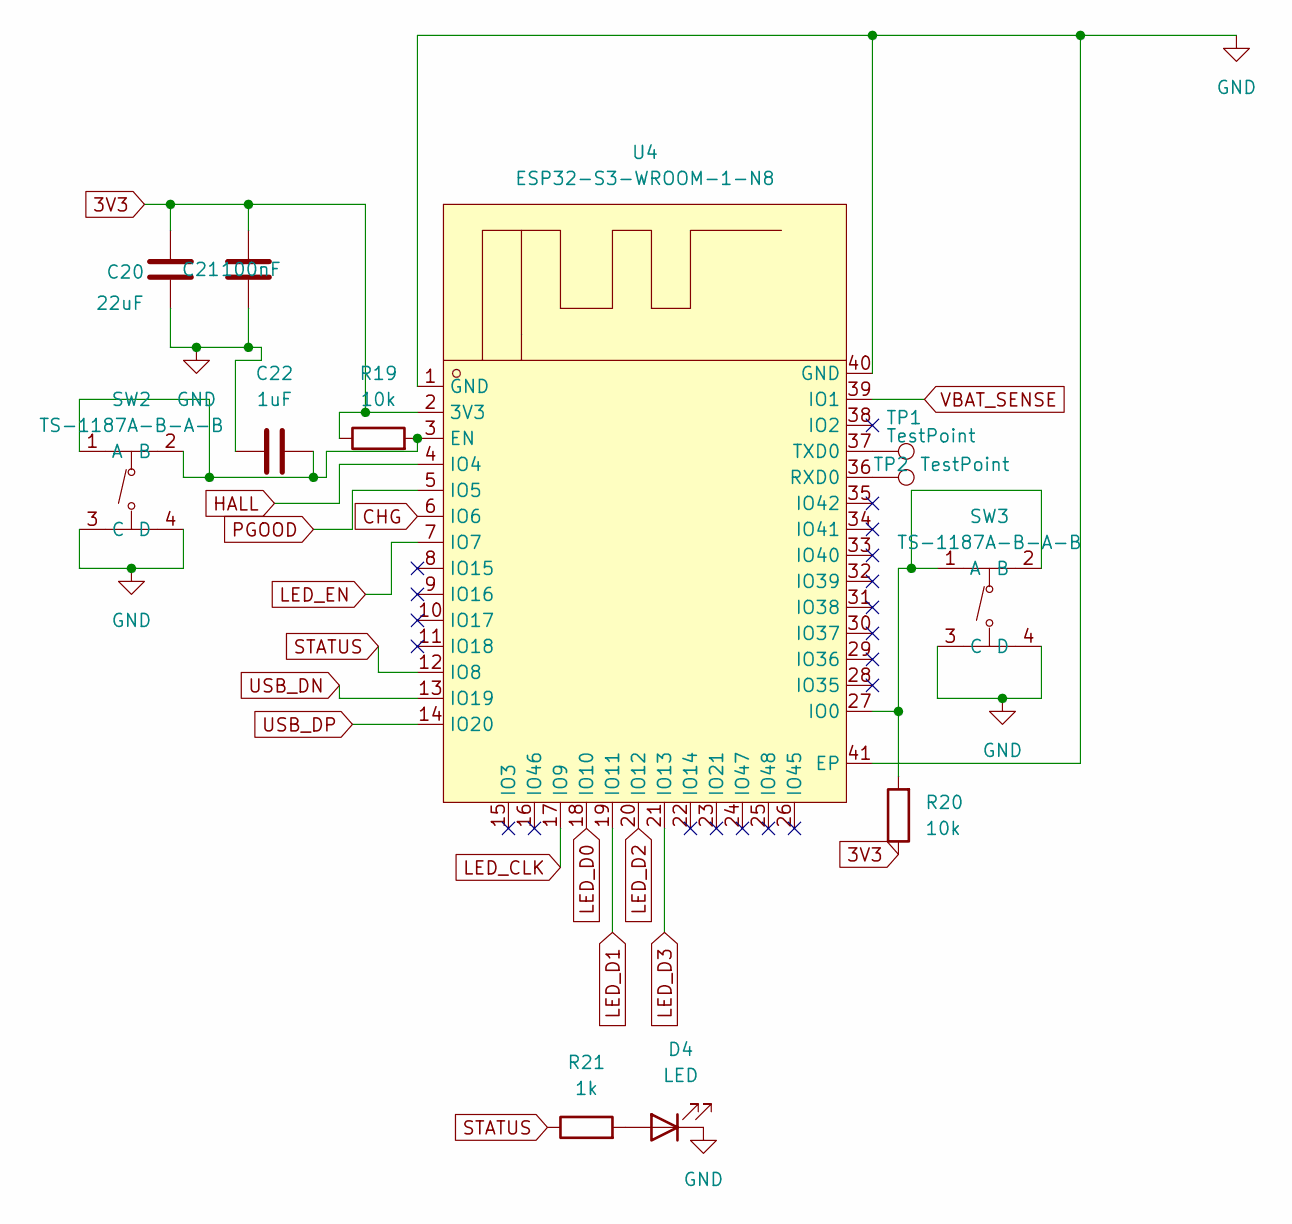
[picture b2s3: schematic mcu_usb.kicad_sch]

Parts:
C20: 22uF; C_0805_2012Metric; LCSC Part C45783
C21: 100nF; C_0402_1005Metric; LCSC Part C1525
C22: 1uF; C_0402_1005Metric; LCSC Part C52923
D4: LED; LED_0603_1608Metric; LCSC Part C2286
R19, R20: 10k; R_0402_1005Metric; LCSC Part C25744
R21: 1k; R_0402_1005Metric; LCSC Part C11702
SW2, SW3: TS-1187A-B-A-B; SW-SMD_4P-L5.1-W5.1-P3.70-LS6.5-TL_H1.5; MPN TS-1187A-B-A-B; LCSC Part C318884
TP1, TP2: TestPoint; TestPoint_Pad_D1.0mm
U4: ESP32-S3-WROOM-1-N8; WIFIM-SMD_ESP32-S3-WROOM-1-N8; MPN ESP32-S3-WROOM-1-N8; LCSC Part C2913198

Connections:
3V3: C20.1, C21.1, R19.1, R20.1, U4.2 (3V3); also elsewhere on the board
CHG: U4.6 (IO6); also elsewhere on the board
GND: C20.2, C21.2, C22.1, D4.1 (K), SW2.3 (C), SW2.4 (D), SW3.3 (C), SW3.4 (D), U4.1 (GND), U4.40 (GND), U4.41 (EP); also elsewhere on the board
HALL: U4.4 (IO4); also elsewhere on the board
LED_CLK: U4.17 (IO9); also elsewhere on the board
LED_D0: U4.18 (IO10); also elsewhere on the board
LED_D1: U4.19 (IO11); also elsewhere on the board
LED_D2: U4.20 (IO12); also elsewhere on the board
LED_D3: U4.21 (IO13); also elsewhere on the board
LED_EN: U4.7 (IO7); also elsewhere on the board
unnamed: D4.2 (A), R21.2
unnamed: C22.2, R19.2, SW2.1 (A), SW2.2 (B), U4.3 (EN)
unnamed: R20.2, SW3.1 (A), SW3.2 (B), U4.27 (IO0)
unnamed: TP2.1 (1_1), U4.36 (RXD0)
unnamed: TP1.1 (1_1), U4.37 (TXD0)
PGOOD: U4.5 (IO5); also elsewhere on the board
STATUS: R21.1, U4.12 (IO8)
USB_DN: U4.13 (IO19); also elsewhere on the board
USB_DP: U4.14 (IO20); also elsewhere on the board
VBAT_SENSE: U4.39 (IO1); also elsewhere on the board
